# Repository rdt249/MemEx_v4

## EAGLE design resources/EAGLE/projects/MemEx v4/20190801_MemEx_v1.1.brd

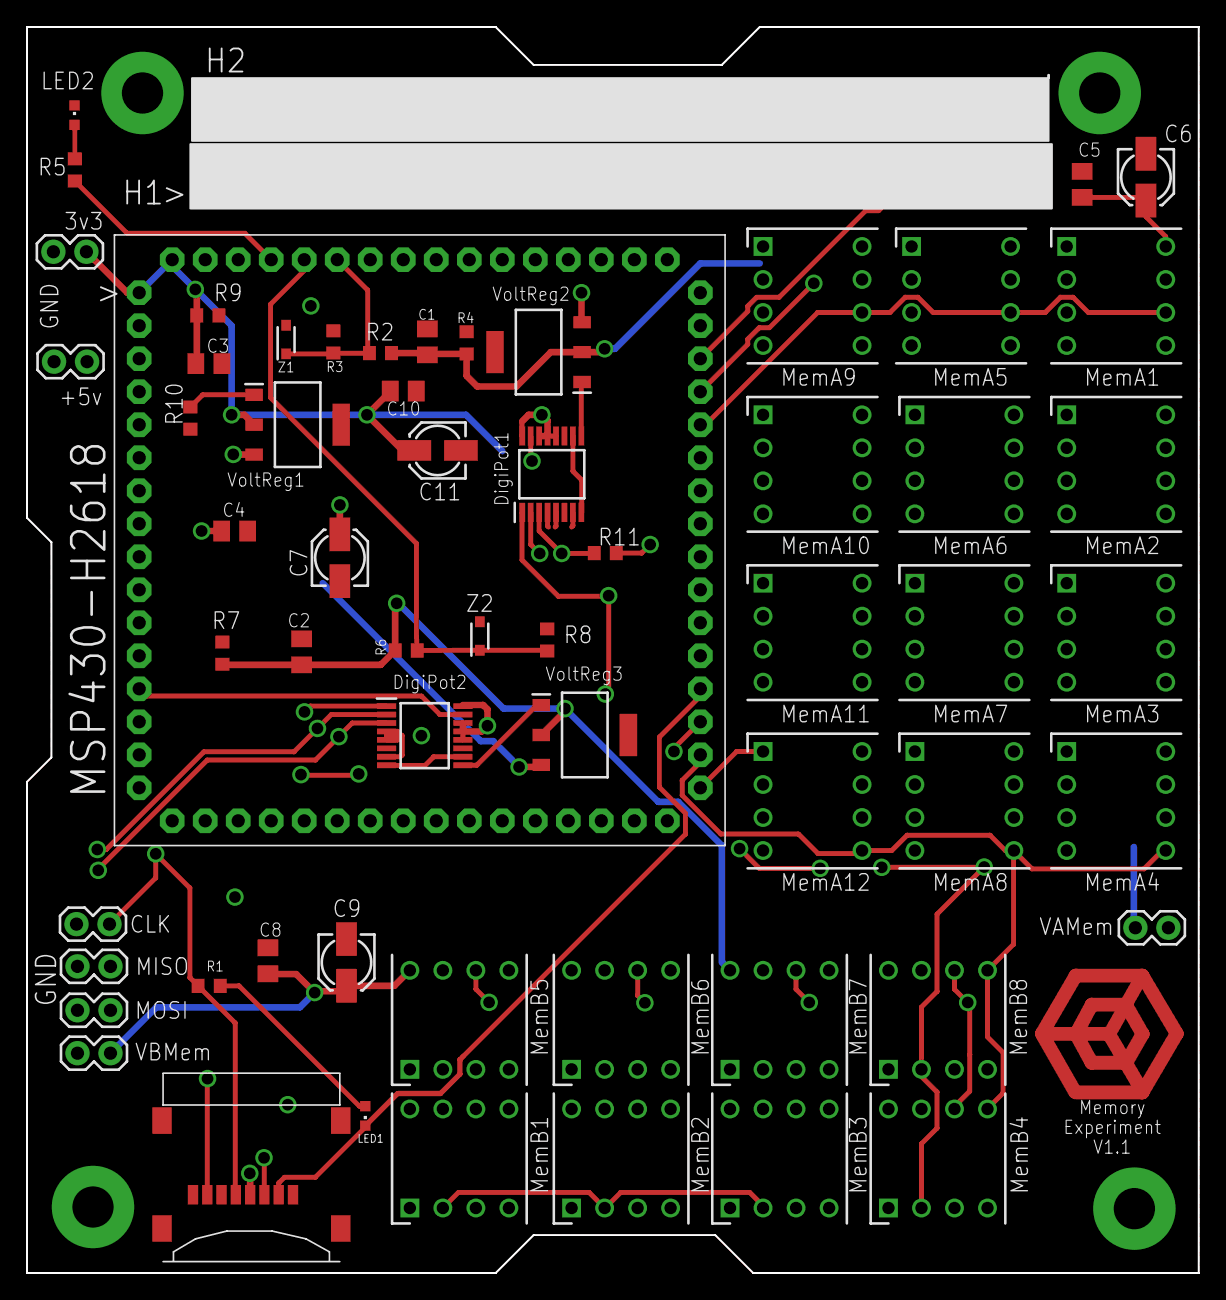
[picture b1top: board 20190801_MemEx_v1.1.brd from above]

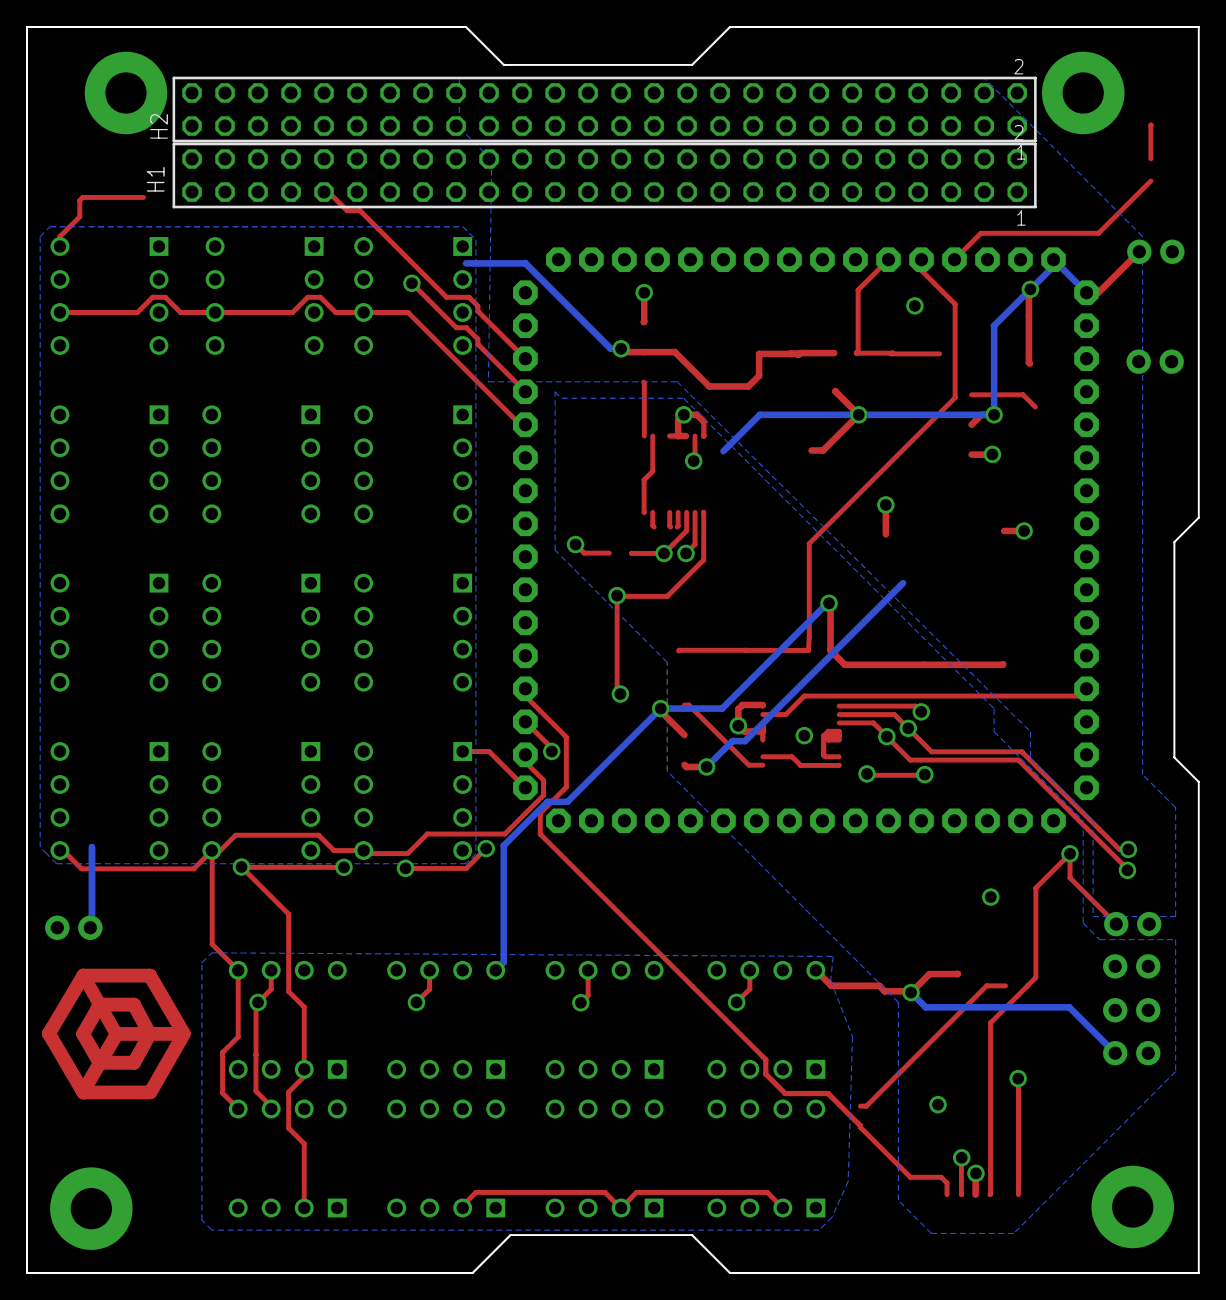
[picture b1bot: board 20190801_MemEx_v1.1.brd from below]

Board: 4 copper layers, 90.2 x 95.9 mm, 62 parts (2 on the bottom side), 44 nets.

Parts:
C1, C2, C3: 4.7u; C0805K
C4, C5, C8, C10: 1u; C0805K
C6, C7, C9, C11: 0.1u; 153CLV-0405
H1: H1; TSW-126-XX-G-D
H2: H2; TSW-126-XX-G-D
IC1, IC16: AD5235BRUZ250; SOP65P640X120-16N
IC2, IC15, IC25: LT3080EST#PBF; SOT230P700X180-4N
IC3, IC4, IC5, IC6, IC7, IC8, IC9, IC10, IC11, IC12, IC13, IC14, IC17, IC18, IC19, IC20, IC21, IC22, IC23, IC24: 1-2199298-2; DIPS762W70P254L1016H510Q8N
J1: 47219-2001; MOLEX_47219-2001
J2, J3, J4, J5, J6, J7, J8: 1X02
LED1: RED 0603; CHIPLED_0603
LED2: GREEN 0603; CHIPLED_0603
R1, R4, R5, R7, R9: 470; R0603
R2, R6: 3.4k; R0603
R3, R8: 6.65k; R0603
R10: 330k; R0603
R11: 2.2k; R0603
U$1: MSP430-H2618
Z1, Z2: 3.43V; SODFL2513X70N

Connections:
3V3: C3.1, C10.1, C11.+, IC1.12, IC1.13, IC1.14, IC1.16, IC16.12, IC16.13, IC16.14, IC16.16, IC25.2, J1.4, J4.2, R9.2, R11.2, U$1.P1, U$1.P64
3V3SET: IC25.1, R10.2
18/D3/SCL: H1.43, U$1.P46
19/D2/SDA: H1.41, U$1.P45
+5V: C4.1, C7.+, H2.34, IC2.3, IC15.3, IC25.3, J3.2
CLK: IC1.1, IC3.6, IC4.6, IC5.6, IC6.6, IC7.6, IC8.6, IC9.6, IC10.6, IC11.6, IC12.6, IC13.6, IC14.6, IC16.1, IC17.6, IC18.6, IC19.6, IC20.6, IC21.6, IC22.6, IC23.6, IC24.6, J1.5, J8.2, R1.1, U$1.P44
CS1_1: IC14.1, U$1.P22
CS1_2: IC13.1, U$1.P23
CS1_3: IC12.1, U$1.P24
CS1_4: IC11.1, U$1.P25
CS1_5: IC10.1, U$1.P26
CS1_6: IC9.1, U$1.P27
CS1_7: IC8.1, U$1.P28
CS1_8: IC7.1, U$1.P29
CS1_9: IC6.1, U$1.P30
CS1_10: IC5.1, U$1.P31
CS1_11: IC4.1, U$1.P32
CS1_12: IC3.1, U$1.P33
CS2_1: IC21.1, U$1.P14
CS2_2: IC22.1, U$1.P15
CS2_3: IC23.1, U$1.P16
CS2_4: IC24.1, U$1.P17
CS2_5: IC17.1, U$1.P18
CS2_6: IC18.1, U$1.P19
CS2_7: IC19.1, U$1.P20
CS2_8: IC20.1, U$1.P21
CS_POT1: IC1.15, U$1.P12
CS_POT2: IC16.15, U$1.P13
CS_SD: J1.2, LED1.C, U$1.P36
GND: C1.2, C2.2, C3.2, C4.2, C5.2, C6.-, C7.-, C8.2, C9.-, C10.2, C11.-, H2.29, H2.30, H2.32, IC1.4, IC1.5, IC1.7, IC3.4, IC4.4, IC5.4, IC6.4, IC7.4, IC8.4, IC9.4, IC10.4, IC11.4, IC12.4, IC13.4, IC14.4, IC16.4, IC16.5, IC16.7, IC17.4, IC18.4, IC19.4, IC20.4, IC21.4, IC22.4, IC23.4, IC24.4, J1.6, J1.G1, J1.G2, J1.G3, J1.G4, J2.1, J3.1, J4.1, J5.1, J6.1, J7.1, J8.1, LED2.C, R3.1, R4.1, R7.1, R8.1, R9.1, R10.1, U$1.P62, U$1.P63, Z1.2, Z2.2
MEMVOLT1: C1.1, C5.1, C6.+, IC2.2, IC3.7, IC3.8, IC4.7, IC4.8, IC5.7, IC5.8, IC6.7, IC6.8, IC7.7, IC7.8, IC8.7, IC8.8, IC9.7, IC9.8, IC10.7, IC10.8, IC11.7, IC11.8, IC12.7, IC12.8, IC13.7, IC13.8, IC14.7, IC14.8, J5.2, R2.2, R4.2
MEMVOLT2: C2.1, C8.1, C9.+, IC15.2, IC17.7, IC17.8, IC18.7, IC18.8, IC19.7, IC19.8, IC20.7, IC20.8, IC21.7, IC21.8, IC22.7, IC22.8, IC23.7, IC23.8, IC24.7, IC24.8, J6.2, R6.2, R7.2
MISO: IC1.3, IC3.2, IC4.2, IC5.2, IC6.2, IC7.2, IC8.2, IC9.2, IC10.2, IC11.2, IC12.2, IC13.2, IC14.2, IC16.3, IC17.2, IC18.2, IC19.2, IC20.2, IC21.2, IC22.2, IC23.2, IC24.2, J1.7, J2.2, R11.1, U$1.P35
MOSI: IC1.2, IC3.5, IC4.5, IC5.5, IC6.5, IC7.5, IC8.5, IC9.5, IC10.5, IC11.5, IC12.5, IC13.5, IC14.5, IC16.2, IC17.5, IC18.5, IC19.5, IC20.5, IC21.5, IC22.5, IC23.5, IC24.5, J1.3, J7.2, U$1.P34
unnamed: R5.2, U$1.P61
unnamed: LED2.A, R5.1
unnamed: LED1.A, R1.2
unnamed: R6.1, R8.2, U$1.P60, Z2.1
unnamed: IC14.3, U$1.P7
unnamed: R2.1, R3.2, U$1.P59, Z1.1
POTVOLT1: IC1.9, IC2.1
POTVOLT2: IC15.1, IC16.9
TESTVOLT1: IC1.8, IC1.10
TESTVOLT2: IC16.8, IC16.10

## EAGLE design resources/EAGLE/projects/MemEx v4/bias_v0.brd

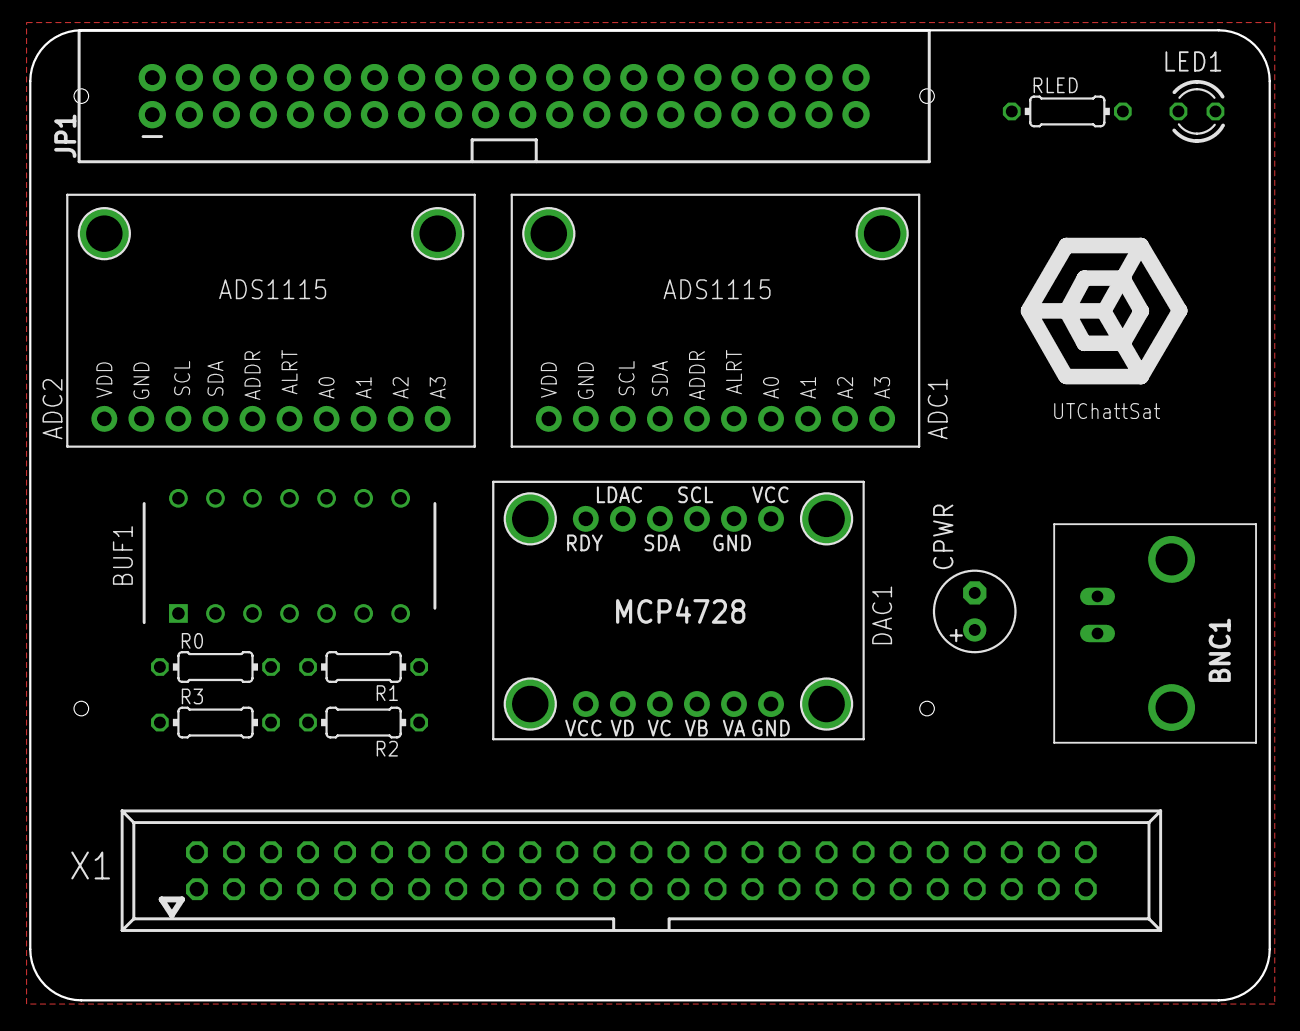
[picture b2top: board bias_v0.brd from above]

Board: 2 copper layers, 85.0 x 66.5 mm, 23 parts (0 on the bottom side), 19 nets, no tracks yet.

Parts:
BNC1: BNC
BUF1: LM124_PTH; CDIP790W66P254L1954H508Q14
CPWR: E2,5-6
JP1: RASPBERRYPI-40-PIN-GPIO_PTH; 2X20_SHROUDED
JP2, JP5: 1X10_ROUND70
JP3, JP4: 1X06_ROUND_70
LED1: LED3MM
R0, R1, R2, R3: 0204/7
RLED: 0204/7
U$3, U$4, U$5, U$6, U$7, U$8, U$15, U$16: MOUNTINGHOLE2.5; MOUNTINGHOLE_2.5_PLATED
X1: PARALLEL COMMS; 057-050-1

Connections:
3V3: JP1.1, JP1.17, JP2.10, JP3.1, JP4.6, JP5.10
+5V: BNC1.S, BUF1.4, CPWR.+, JP1.2, JP1.4
GND: BNC1.GND, BUF1.11, CPWR.-, JP1.6, JP1.9, JP1.14, JP1.20, JP1.25, JP1.30, JP1.34, JP1.39, JP2.9, JP3.2, JP4.1, JP5.9, RLED.1, X1.5, X1.6
unnamed: JP1.37, LED1.A
unnamed: LED1.K, RLED.2
SCL: JP1.5, JP2.8, JP3.3, JP5.8
SDA: JP1.3, JP2.7, JP3.4, JP5.7
VBUF0: BUF1.1, BUF1.2, JP2.4, R0.1
VBUF1: BUF1.6, BUF1.7, JP2.3, R1.1
VBUF2: BUF1.8, BUF1.9, JP2.2, R2.1
VBUF3: BUF1.13, BUF1.14, JP2.1, R3.1
VDAC0: BUF1.3, JP4.2
VDAC1: BUF1.5, JP4.3
VDAC2: BUF1.10, JP4.4
VDAC3: BUF1.12, JP4.5
VOUT0: JP5.4, R0.2, X1.1
VOUT1: JP5.3, R1.2, X1.2
VOUT2: JP5.2, R2.2, X1.3
VOUT3: JP5.1, R3.2, X1.4

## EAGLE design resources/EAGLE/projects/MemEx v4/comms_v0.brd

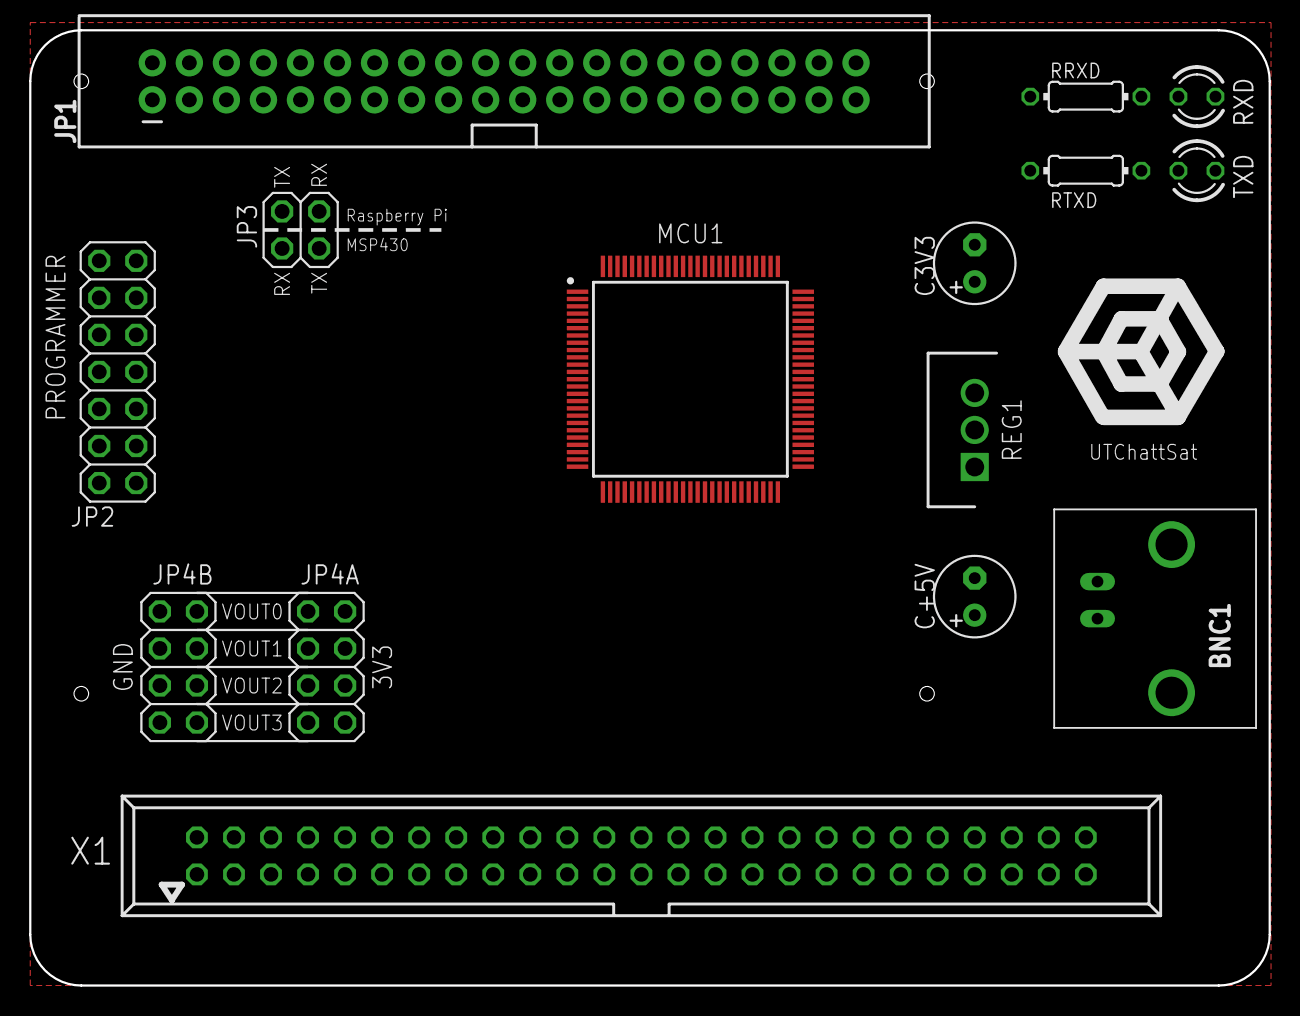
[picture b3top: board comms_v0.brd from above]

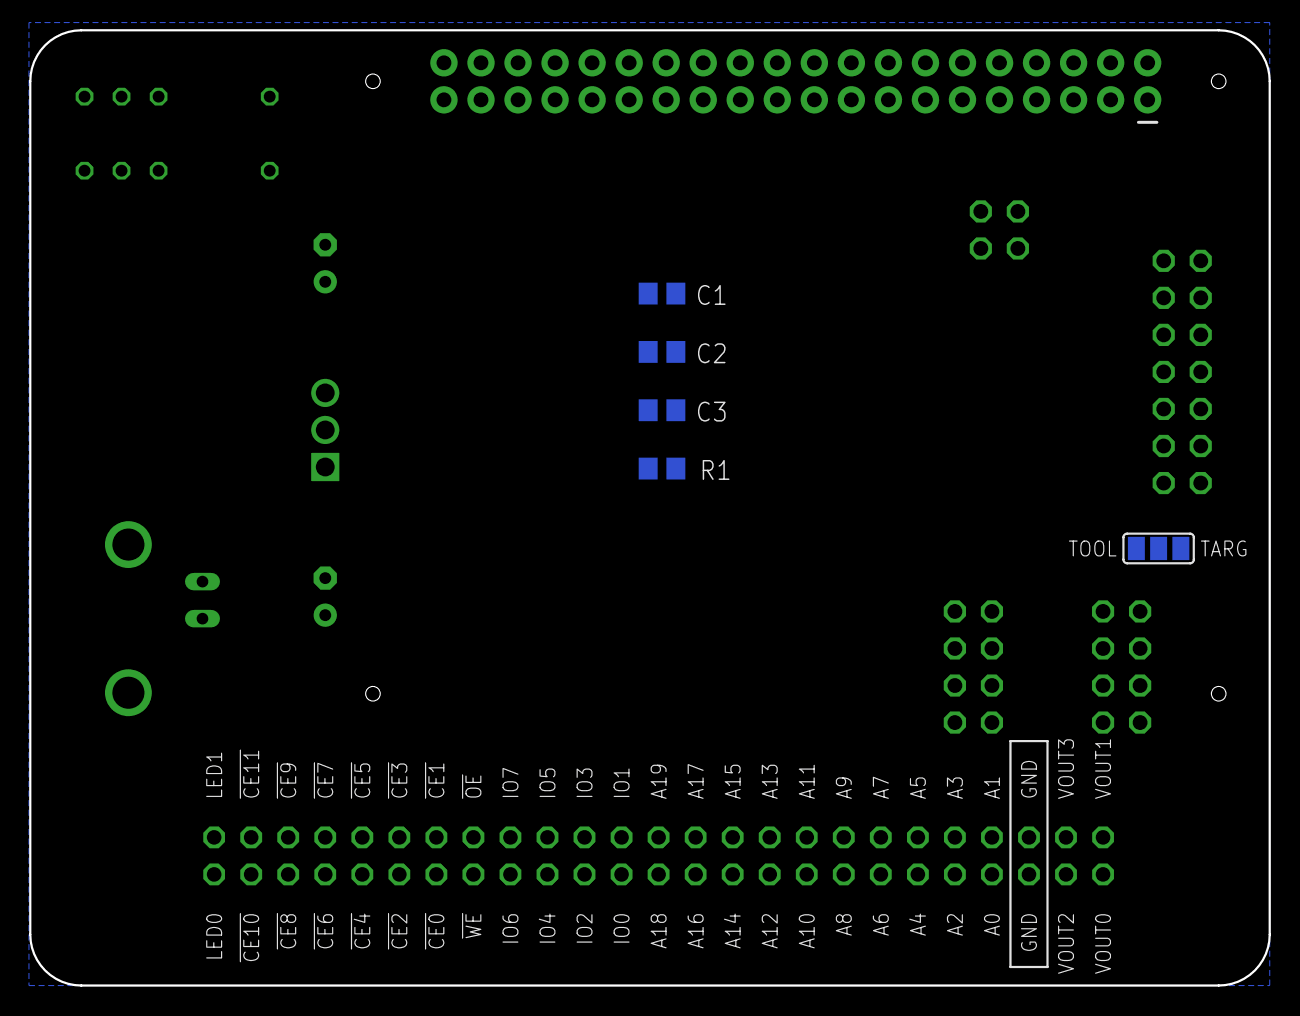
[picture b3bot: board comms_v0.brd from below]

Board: 2 copper layers, 85.0 x 65.5 mm, 20 parts (5 on the bottom side), 64 nets, no tracks yet.

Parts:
BNC1: BNC
C1: 10u; C0805
C2: 0.1u; C0805
C3: 2.2n; C0805
C3V3: E2,5-6
C+5V: E2,5-6
JP1: RASPBERRYPI-40-PIN-GPIO_PTH; 2X20_SHROUDED
JP2: 2X07
JP3: 2X02
JP4A, JP4B: 2X04
MCU1: MSP430FR6989; QFP50P1600X1600X160-100N
R1: 47k; R0805
REG1: LM3940; TO254P470X1028X1955-3P
RRXD: 0204/7
RTXD: 0204/7
RXD: LED3MM
SJ1: SJ_2
TXD: LED3MM
X1: PARALLEL COMMS; 057-050-1

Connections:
3V3: C1.1, C2.1, C3V3.+, JP1.1, JP1.17, JP4A.1, JP4A.3, JP4A.5, JP4A.7, MCU1.27, MCU1.58, MCU1.75, MCU1.79, MCU1.99, R1.2, REG1.3, SJ1.2
!CE0: MCU1.52, X1.37
!CE1: MCU1.53, X1.38
!CE2: MCU1.54, X1.39
!CE3: MCU1.55, X1.40
!CE4: MCU1.56, X1.41
!CE5: MCU1.35, X1.42
!CE6: MCU1.36, X1.43
!CE7: MCU1.38, X1.44
!CE8: MCU1.44, X1.45
!CE9: MCU1.45, X1.46
!CE10: MCU1.46, X1.47
!CE11: MCU1.47, X1.48
!OE: MCU1.8, X1.36
!RST: C3.1, JP2.11, MCU1.29, R1.1
!WE: MCU1.7, X1.35
+5V: BNC1.S, C+5V.+, JP1.2, JP1.4, REG1.1
A0: MCU1.23, X1.7
A1: MCU1.24, X1.8
A2: MCU1.25, X1.9
A3: MCU1.39, X1.10
A4: MCU1.40, X1.11
A5: MCU1.41, X1.12
A6: MCU1.42, X1.13
A7: MCU1.43, X1.14
A8: MCU1.96, X1.15
A9: MCU1.97, X1.16
A10: MCU1.100, X1.17
A11: MCU1.1, X1.18
A12: MCU1.91, X1.19
A13: MCU1.92, X1.20
A14: MCU1.93, X1.21
A15: MCU1.94, X1.22
A16: MCU1.19, X1.23
A17: MCU1.20, X1.24
A18: MCU1.21, X1.25
A19: MCU1.22, X1.26
GND: BNC1.GND, C1.2, C2.2, C3.2, C3V3.-, C+5V.-, JP1.6, JP1.9, JP1.14, JP1.20, JP1.25, JP1.30, JP1.34, JP1.39, JP2.9, JP4B.2, JP4B.4, JP4B.6, JP4B.8, MCU1.26, MCU1.57, MCU1.76, MCU1.80, MCU1.83, MCU1.86, MCU1.98, REG1.2, RRXD.1, RTXD.1, X1.5, X1.6
IO0: MCU1.66, X1.27
IO1: MCU1.65, X1.28
IO2: MCU1.64, X1.29
IO3: MCU1.63, X1.30
IO4: MCU1.2, X1.31
IO5: MCU1.3, X1.32
IO6: MCU1.4, X1.33
IO7: MCU1.5, X1.34
LED0: MCU1.74, X1.49
MCU_RXD: JP3.1, MCU1.50, RXD.A
MCU_TXD: JP3.3, MCU1.51, TXD.A
unnamed: RTXD.2, TXD.K
unnamed: RRXD.2, RXD.K
RPI_RXD: JP1.10, JP3.4
RPI_TXD: JP1.8, JP3.2
TCK: JP2.7, MCU1.33
TDI: JP2.3, MCU1.31
TDO: JP2.1, MCU1.30
TEST: JP2.8, MCU1.28
TMS: JP2.5, MCU1.32
VCCTARGET: JP2.4, SJ1.1
VCCTOOL: JP2.2, SJ1.3
VOUT0: JP4A.8, JP4B.7, MCU1.67, X1.1
VOUT1: JP4A.6, JP4B.5, MCU1.68, X1.2
VOUT2: JP4A.4, JP4B.3, MCU1.69, X1.3
VOUT3: JP4A.2, JP4B.1, MCU1.70, X1.4

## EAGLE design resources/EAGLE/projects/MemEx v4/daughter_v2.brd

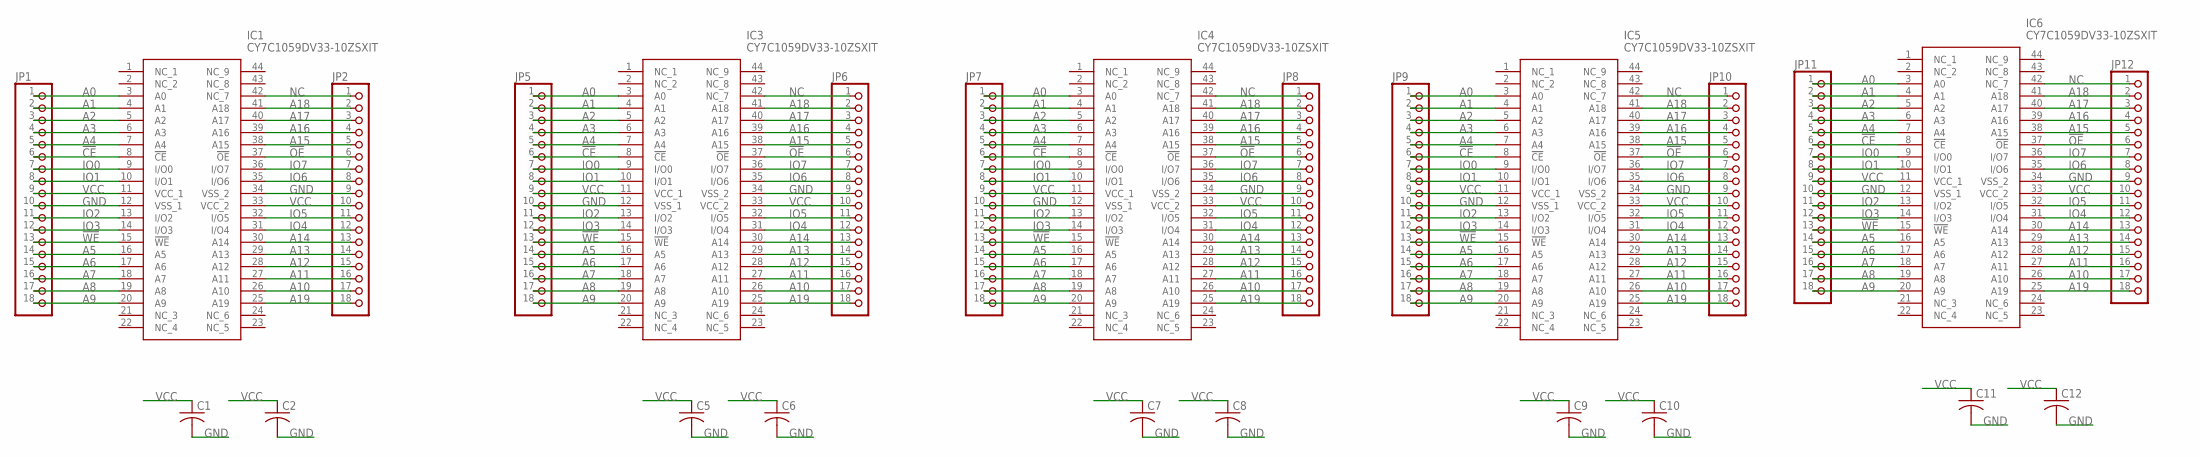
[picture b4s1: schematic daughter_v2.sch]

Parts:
C1, C2, C5, C6, C7, C8, C9, C10, C11, C12: C-USC0805; C0805
IC1, IC3, IC4, IC5, IC6: CY7C1059DV33-10ZSXIT; SOP80P1184X119-44N
JP1, JP2, JP5, JP6, JP7, JP8, JP9, JP10, JP11, JP12: PINHD-1X18; 1X18

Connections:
!CE: IC1.8 (!CE), IC3.8 (!CE), IC4.8 (!CE), IC5.8 (!CE), IC6.8 (!CE), JP1.6, JP5.6, JP7.6, JP9.6, JP11.6
!OE: IC1.37 (!OE), IC3.37 (!OE), IC4.37 (!OE), IC5.37 (!OE), IC6.37 (!OE), JP2.6, JP6.6, JP8.6, JP10.6, JP12.6
!WE: IC1.15 (!WE), IC3.15 (!WE), IC4.15 (!WE), IC5.15 (!WE), IC6.15 (!WE), JP1.13, JP5.13, JP7.13, JP9.13, JP11.13
A0: IC1.3 (A0), IC3.3 (A0), IC4.3 (A0), IC5.3 (A0), IC6.3 (A0), JP1.1, JP5.1, JP7.1, JP9.1, JP11.1
A1: IC1.4 (A1), IC3.4 (A1), IC4.4 (A1), IC5.4 (A1), IC6.4 (A1), JP1.2, JP5.2, JP7.2, JP9.2, JP11.2
A2: IC1.5 (A2), IC3.5 (A2), IC4.5 (A2), IC5.5 (A2), IC6.5 (A2), JP1.3, JP5.3, JP7.3, JP9.3, JP11.3
A3: IC1.6 (A3), IC3.6 (A3), IC4.6 (A3), IC5.6 (A3), IC6.6 (A3), JP1.4, JP5.4, JP7.4, JP9.4, JP11.4
A4: IC1.7 (A4), IC3.7 (A4), IC4.7 (A4), IC5.7 (A4), IC6.7 (A4), JP1.5, JP5.5, JP7.5, JP9.5, JP11.5
A5: IC1.16 (A5), IC3.16 (A5), IC4.16 (A5), IC5.16 (A5), IC6.16 (A5), JP1.14, JP5.14, JP7.14, JP9.14, JP11.14
A6: IC1.17 (A6), IC3.17 (A6), IC4.17 (A6), IC5.17 (A6), IC6.17 (A6), JP1.15, JP5.15, JP7.15, JP9.15, JP11.15
A7: IC1.18 (A7), IC3.18 (A7), IC4.18 (A7), IC5.18 (A7), IC6.18 (A7), JP1.16, JP5.16, JP7.16, JP9.16, JP11.16
A8: IC1.19 (A8), IC3.19 (A8), IC4.19 (A8), IC5.19 (A8), IC6.19 (A8), JP1.17, JP5.17, JP7.17, JP9.17, JP11.17
A9: IC1.20 (A9), IC3.20 (A9), IC4.20 (A9), IC5.20 (A9), IC6.20 (A9), JP1.18, JP5.18, JP7.18, JP9.18, JP11.18
A10: IC1.26 (A10), IC3.26 (A10), IC4.26 (A10), IC5.26 (A10), IC6.26 (A10), JP2.17, JP6.17, JP8.17, JP10.17, JP12.17
A11: IC1.27 (A11), IC3.27 (A11), IC4.27 (A11), IC5.27 (A11), IC6.27 (A11), JP2.16, JP6.16, JP8.16, JP10.16, JP12.16
A12: IC1.28 (A12), IC3.28 (A12), IC4.28 (A12), IC5.28 (A12), IC6.28 (A12), JP2.15, JP6.15, JP8.15, JP10.15, JP12.15
A13: IC1.29 (A13), IC3.29 (A13), IC4.29 (A13), IC5.29 (A13), IC6.29 (A13), JP2.14, JP6.14, JP8.14, JP10.14, JP12.14
A14: IC1.30 (A14), IC3.30 (A14), IC4.30 (A14), IC5.30 (A14), IC6.30 (A14), JP2.13, JP6.13, JP8.13, JP10.13, JP12.13
A15: IC1.38 (A15), IC3.38 (A15), IC4.38 (A15), IC5.38 (A15), IC6.38 (A15), JP2.5, JP6.5, JP8.5, JP10.5, JP12.5
A16: IC1.39 (A16), IC3.39 (A16), IC4.39 (A16), IC5.39 (A16), IC6.39 (A16), JP2.4, JP6.4, JP8.4, JP10.4, JP12.4
A17: IC1.40 (A17), IC3.40 (A17), IC4.40 (A17), IC5.40 (A17), IC6.40 (A17), JP2.3, JP6.3, JP8.3, JP10.3, JP12.3
A18: IC1.41 (A18), IC3.41 (A18), IC4.41 (A18), IC5.41 (A18), IC6.41 (A18), JP2.2, JP6.2, JP8.2, JP10.2, JP12.2
A19: IC1.25 (A19), IC3.25 (A19), IC4.25 (A19), IC5.25 (A19), IC6.25 (A19), JP2.18, JP6.18, JP8.18, JP10.18, JP12.18
GND: C1.2, C2.2, C5.2, C6.2, C7.2, C8.2, C9.2, C10.2, C11.2, C12.2, IC1.12 (VSS_1), IC1.34 (VSS_2), IC3.12 (VSS_1), IC3.34 (VSS_2), IC4.12 (VSS_1), IC4.34 (VSS_2), IC5.12 (VSS_1), IC5.34 (VSS_2), IC6.12 (VSS_1), IC6.34 (VSS_2), JP1.10, JP2.9, JP5.10, JP6.9, JP7.10, JP8.9, JP9.10, JP10.9, JP11.10, JP12.9
IO0: IC1.9 (I/O0), IC3.9 (I/O0), IC4.9 (I/O0), IC5.9 (I/O0), IC6.9 (I/O0), JP1.7, JP5.7, JP7.7, JP9.7, JP11.7
IO1: IC1.10 (I/O1), IC3.10 (I/O1), IC4.10 (I/O1), IC5.10 (I/O1), IC6.10 (I/O1), JP1.8, JP5.8, JP7.8, JP9.8, JP11.8
IO2: IC1.13 (I/O2), IC3.13 (I/O2), IC4.13 (I/O2), IC5.13 (I/O2), IC6.13 (I/O2), JP1.11, JP5.11, JP7.11, JP9.11, JP11.11
IO3: IC1.14 (I/O3), IC3.14 (I/O3), IC4.14 (I/O3), IC5.14 (I/O3), IC6.14 (I/O3), JP1.12, JP5.12, JP7.12, JP9.12, JP11.12
IO4: IC1.31 (I/O4), IC3.31 (I/O4), IC4.31 (I/O4), IC5.31 (I/O4), IC6.31 (I/O4), JP2.12, JP6.12, JP8.12, JP10.12, JP12.12
IO5: IC1.32 (I/O5), IC3.32 (I/O5), IC4.32 (I/O5), IC5.32 (I/O5), IC6.32 (I/O5), JP2.11, JP6.11, JP8.11, JP10.11, JP12.11
IO6: IC1.35 (I/O6), IC3.35 (I/O6), IC4.35 (I/O6), IC5.35 (I/O6), IC6.35 (I/O6), JP2.8, JP6.8, JP8.8, JP10.8, JP12.8
IO7: IC1.36 (I/O7), IC3.36 (I/O7), IC4.36 (I/O7), IC5.36 (I/O7), IC6.36 (I/O7), JP2.7, JP6.7, JP8.7, JP10.7, JP12.7
NC: IC1.42 (NC_7), IC3.42 (NC_7), IC4.42 (NC_7), IC5.42 (NC_7), IC6.42 (NC_7), JP2.1, JP6.1, JP8.1, JP10.1, JP12.1
VCC: C1.1, C2.1, C5.1, C6.1, C7.1, C8.1, C9.1, C10.1, C11.1, C12.1, IC1.11 (VCC_1), IC1.33 (VCC_2), IC3.11 (VCC_1), IC3.33 (VCC_2), IC4.11 (VCC_1), IC4.33 (VCC_2), IC5.11 (VCC_1), IC5.33 (VCC_2), IC6.11 (VCC_1), IC6.33 (VCC_2), JP1.9, JP2.10, JP5.9, JP6.10, JP7.9, JP8.10, JP9.9, JP10.10, JP11.9, JP12.10

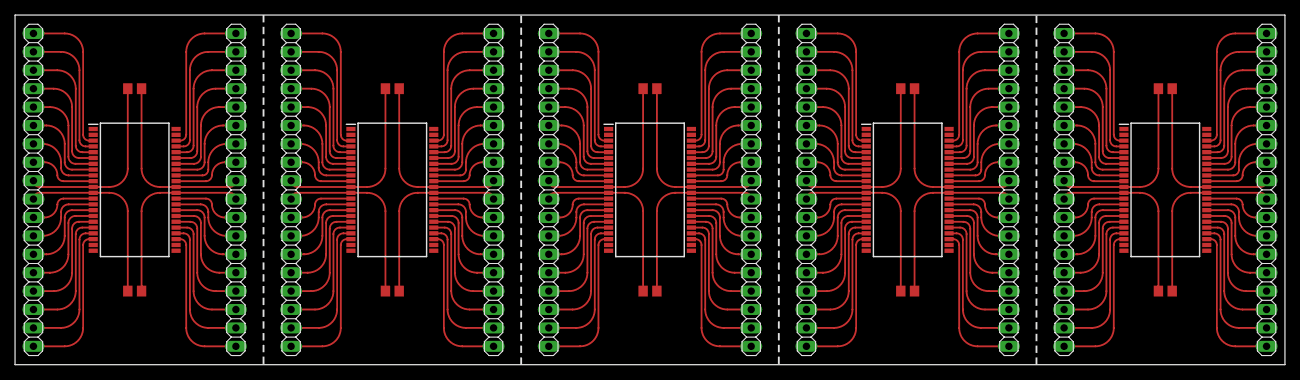
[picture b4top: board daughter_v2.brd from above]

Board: 2 copper layers, 175.3 x 48.3 mm, 25 parts (0 on the bottom side), 34 nets.

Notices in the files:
parts and their libraries:
SparkFun-Connectors: Licensing: Creative Commons ShareAlike 4.0 International - https://creativecommons.org/licenses/by-sa/4.0
microbuilder: This work is placed in the public domain, and may be freely used for commercial and non-commercial work with the following conditions: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
